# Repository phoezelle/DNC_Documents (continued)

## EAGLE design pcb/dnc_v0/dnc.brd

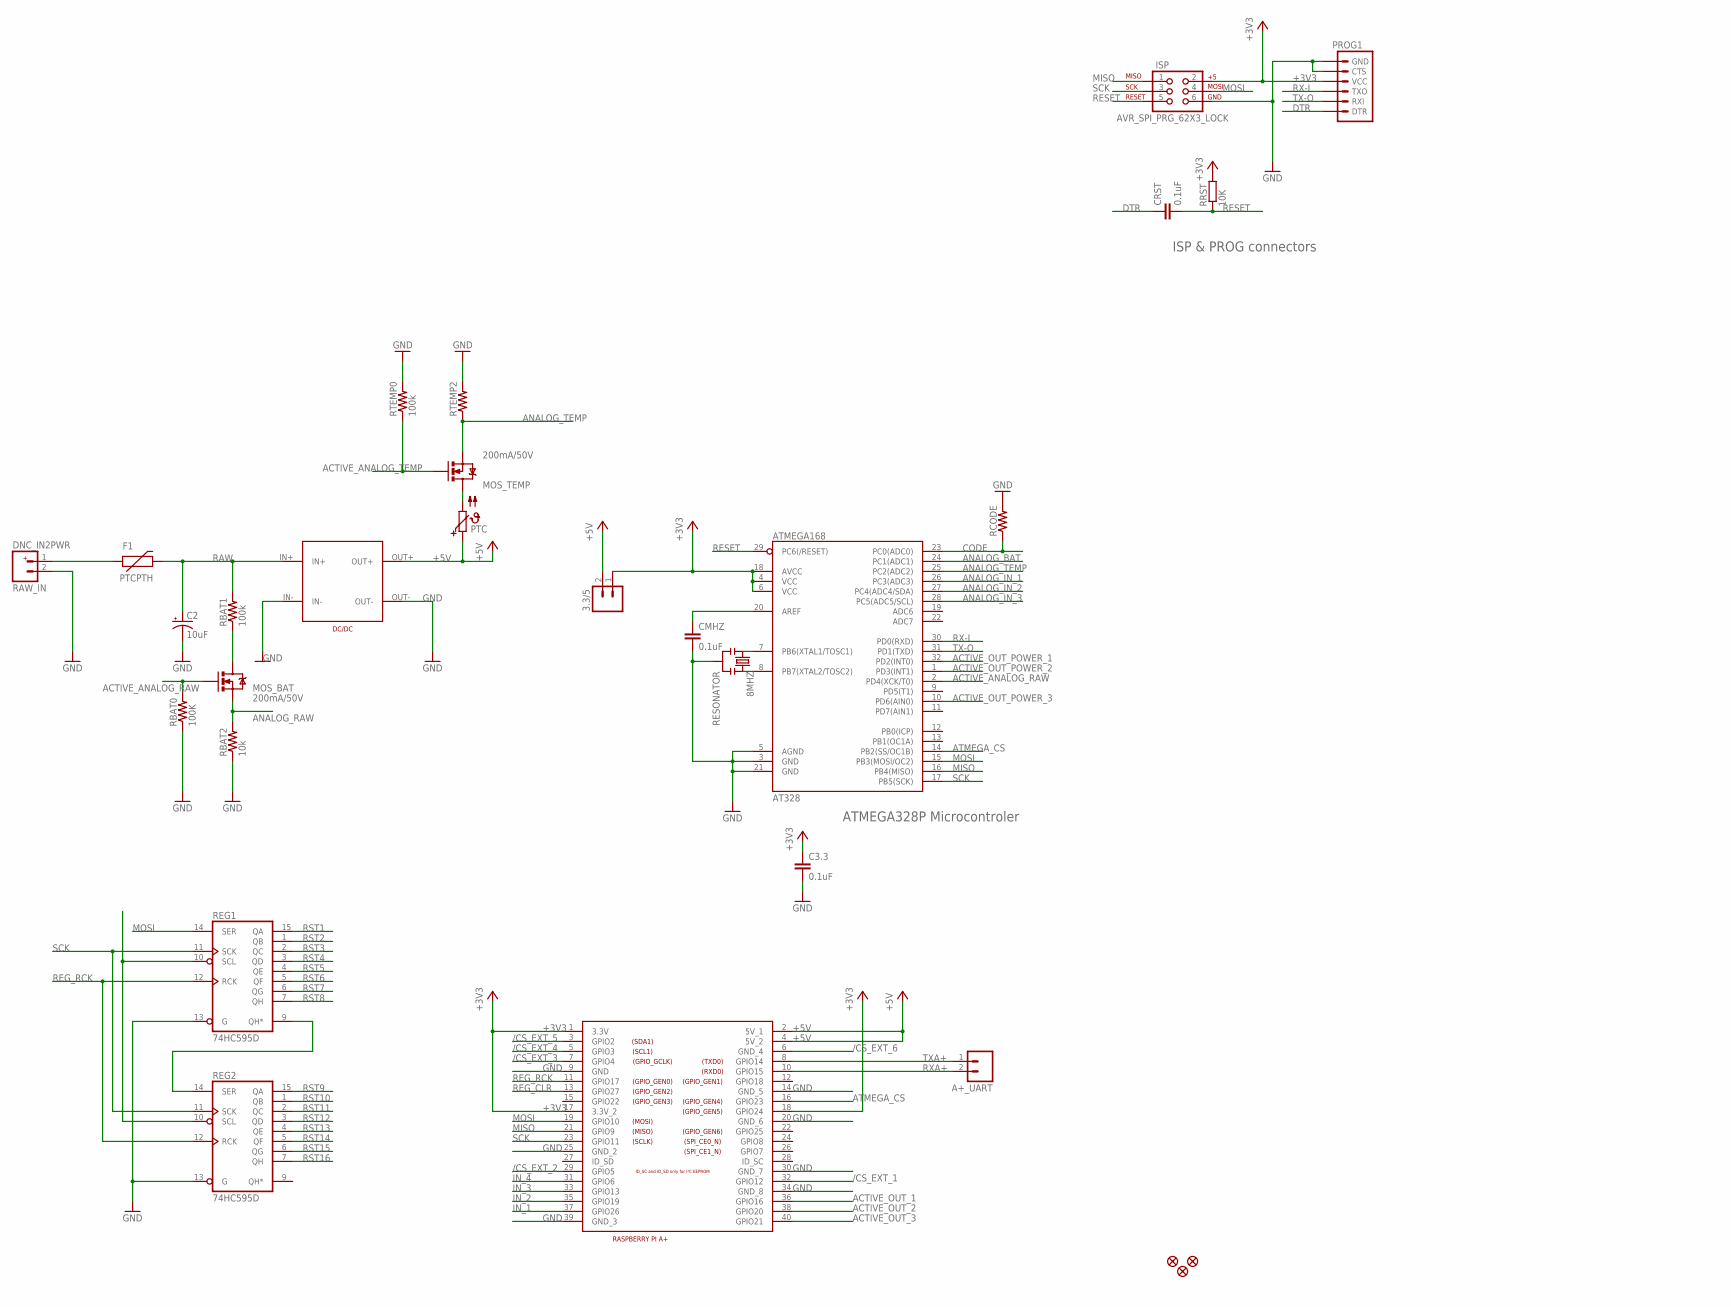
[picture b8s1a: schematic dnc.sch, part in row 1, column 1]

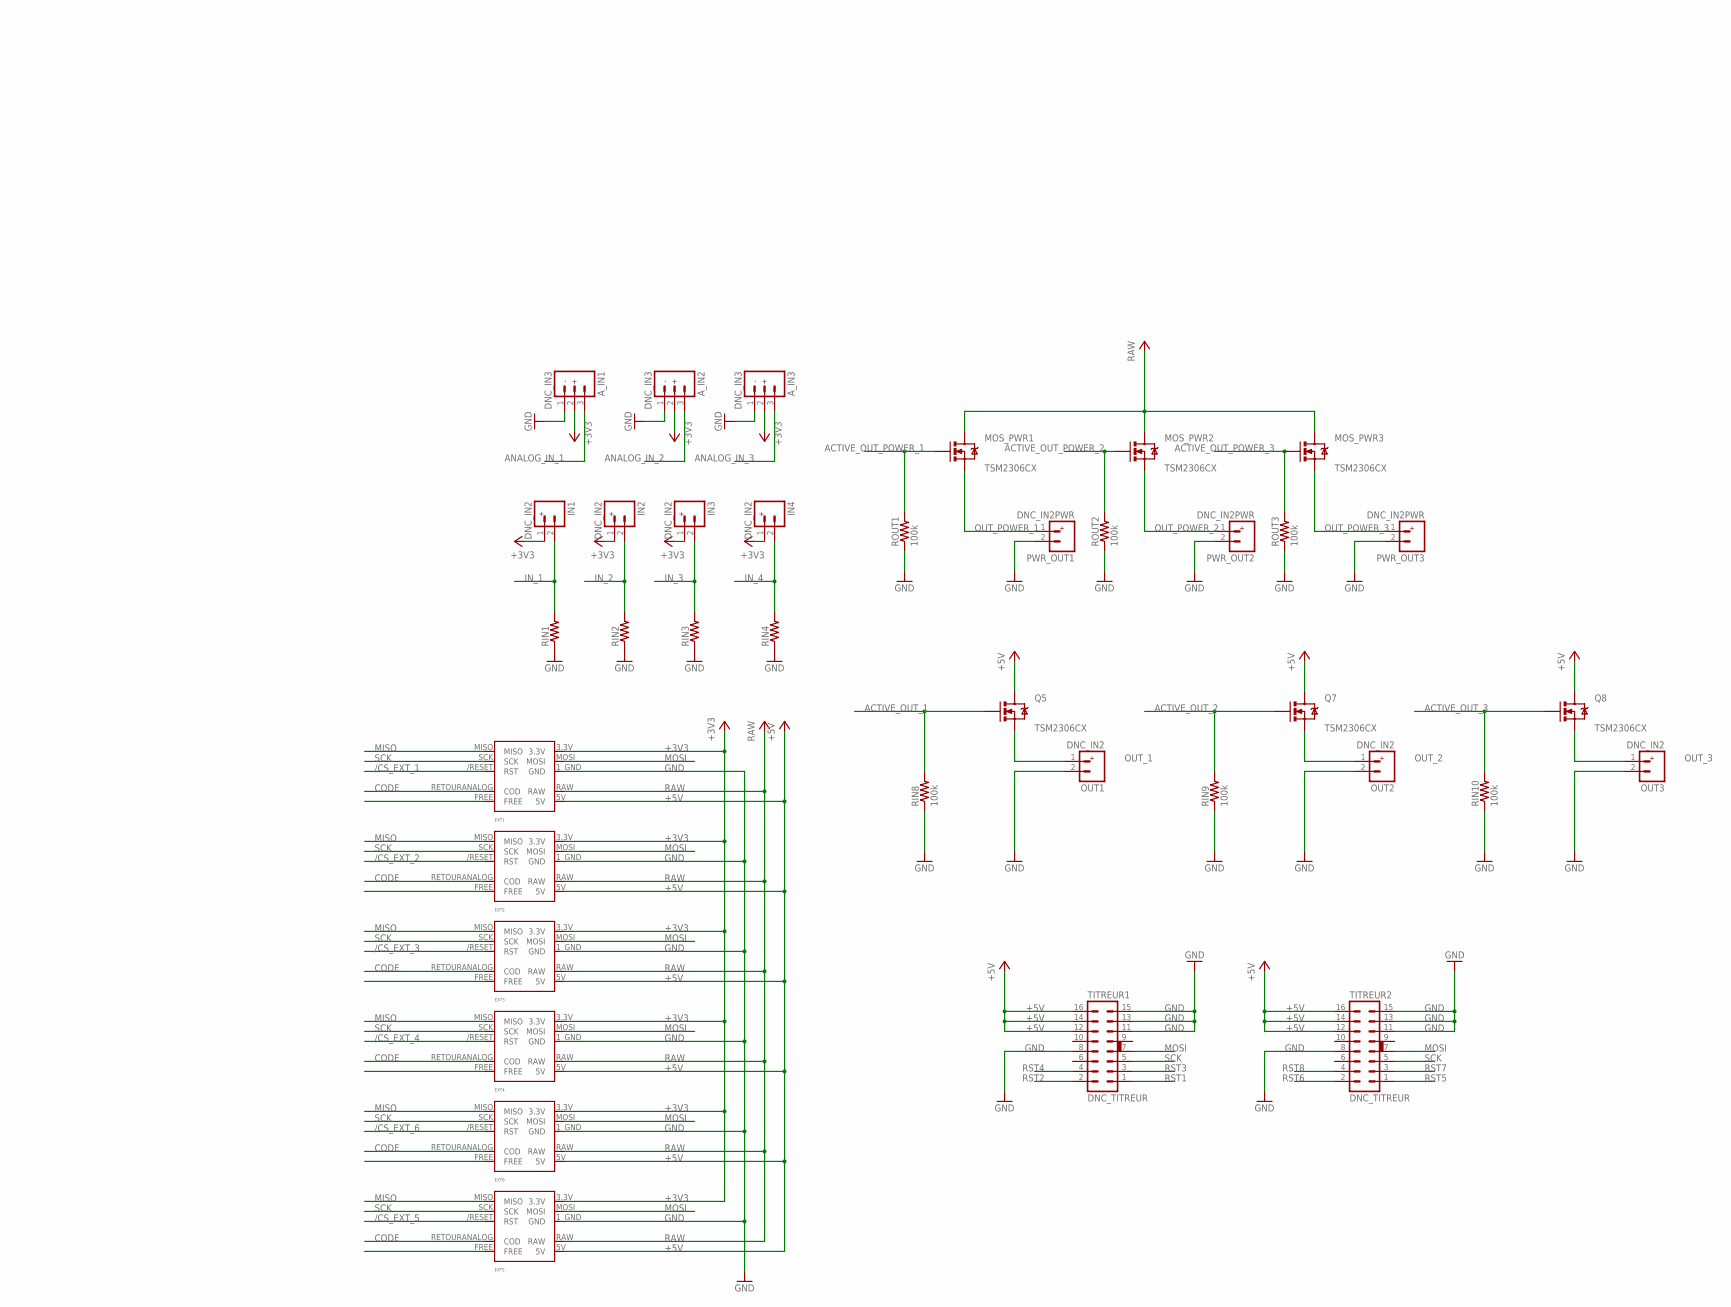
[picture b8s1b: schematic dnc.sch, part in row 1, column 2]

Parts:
3.3/5: M02PTH3; 1X02_LONGPADS
8MHZ: RESONATOR; RESONATOR_7MM
A+_UART: M02LOCK_LONGPADS; 1X02_LOCK_LONGPADS
AT328: ATMEGA168; TQFP32-08
A_IN1, A_IN2, A_IN3: DNC_IN3
C2: 10uF; EIA3216
C3.3: 0.1uF; C0805
CMHZ: 0.1uF; C0805
CRST: 0.1uF; C0805
EXT1, EXT2, EXT3, EXT4, EXT5, EXT6: EXT-DNC; EXTPINDNC
F1: PTCPTH; PTC
IN1, IN2, IN3, IN4: DNC_IN2
ISP: AVR_SPI_PRG_62X3_LOCK; 2X3_LOCK
JP13, JP14, JP19: FIDUCIAL1X2.5; FIDUCIAL-1X2.5
MOS_BAT: 200mA/50V; SOT23-3
MOS_PWR1, MOS_PWR2, MOS_PWR3: TSM2306CX; SOT323
MOS_TEMP: 200mA/50V; SOT23-3
OUT1, OUT2, OUT3: DNC_IN2
PROG1: ARDUINO_SERIAL_PROGRAMLOCK; 1X06_LOCK
PTC: PTC679; P679
PWR_OUT1, PWR_OUT2, PWR_OUT3: DNC_IN2PWR; DNC_IN2_PWR
Q5, Q7, Q8: TSM2306CX; SOT323
RAW_IN: DNC_IN2PWR; DNC_IN2_PWR
RBAT0: 100K; 0603-RES
RBAT1: 100k; 0603-RES
RBAT2: 10k; 0603-RES
RCODE: RESISTOR0603-RES; 0603-RES
REG1, REG2: 74HC595D; SO16
RIN1, RIN2, RIN3, RIN4: RESISTOR0603-RES; 0603-RES
RIN8, RIN9, RIN10: 100k; 0603-RES
ROUT1, ROUT2, ROUT3: 100k; 0603-RES
RRST: 10K; R0603
RTEMP0: 100k; 0603-RES
RTEMP2: RESISTOR0603-RES; 0603-RES
TITREUR1, TITREUR2: DNC_TITREUR
U$4: RASPIA+
U$5: DC/DC_SEED

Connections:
+3V3: 3.3/5.1, AT328.4 (VCC), AT328.6 (VCC), AT328.18 (AVCC), A_IN1.2, A_IN2.2, A_IN3.2, C3.3.1, EXT1.3.3V, EXT2.3.3V, EXT3.3.3V, EXT4.3.3V, EXT5.3.3V, EXT6.3.3V, IN1.1, IN2.1, IN3.1, IN4.1, ISP.2, PROG1.4 (VCC), RRST.2, U$4.1 (3.3V), U$4.17 (3.3V_2), U$4.18 (GPIO24)
+5V: 3.3/5.2, EXT1.5V, EXT2.5V, EXT3.5V, EXT4.5V, EXT5.5V, EXT6.5V, PTC.1, Q5.3 (D), Q7.3 (D), Q8.3 (D), TITREUR1.12, TITREUR1.14, TITREUR1.16, TITREUR2.12, TITREUR2.14, TITREUR2.16, U$4.2 (5V_1), U$4.4 (5V_2), U$5.OUT+
/CS_EXT_1: EXT1./RESET (RST), U$4.32 (GPIO12)
/CS_EXT_2: EXT2./RESET (RST), U$4.29 (GPIO5)
/CS_EXT_3: EXT3./RESET (RST), U$4.7 (GPIO4)
/CS_EXT_4: EXT4./RESET (RST), U$4.5 (GPIO3)
/CS_EXT_5: EXT5./RESET (RST), U$4.3 (GPIO2)
/CS_EXT_6: EXT6./RESET (RST), U$4.6 (GND_4)
ACTIVE_ANALOG_RAW: AT328.2 (PD4(XCK/T0)), MOS_BAT.1 (G), RBAT0.2
ACTIVE_ANALOG_TEMP: MOS_TEMP.1 (G), RTEMP0.1
ACTIVE_OUT_1: Q5.1 (G), RIN8.2, U$4.36 (GPIO16)
ACTIVE_OUT_2: Q7.1 (G), RIN9.2, U$4.38 (GPIO20)
ACTIVE_OUT_3: Q8.1 (G), RIN10.2, U$4.40 (GPIO21)
ACTIVE_OUT_POWER_1: AT328.32 (PD2(INT0)), MOS_PWR1.1 (G), ROUT1.2
ACTIVE_OUT_POWER_2: AT328.1 (PD3(INT1)), MOS_PWR2.1 (G), ROUT2.2
ACTIVE_OUT_POWER_3: AT328.10 (PD6(AIN0)), MOS_PWR3.1 (G), ROUT3.2
ANALOG_BAT: AT328.24 (PC1(ADC1))
ANALOG_IN_1: AT328.26 (PC3(ADC3)), A_IN1.3
ANALOG_IN_2: AT328.27 (PC4(ADC4/SDA)), A_IN2.3
ANALOG_IN_3: AT328.28 (PC5(ADC5/SCL)), A_IN3.3
ANALOG_RAW: MOS_BAT.2 (S), RBAT2.2
ANALOG_TEMP: AT328.25 (PC2(ADC2)), MOS_TEMP.2 (S), RTEMP2.1
AREF: AT328.20 (AREF), CMHZ.1
ATMEGA_CS: AT328.14 (PB2(SS/OC1B)), U$4.16 (GPIO23)
CODE: AT328.23 (PC0(ADC0)), EXT1.RETOURANALOG (COD), EXT2.RETOURANALOG (COD), EXT3.RETOURANALOG (COD), EXT4.RETOURANALOG (COD), EXT5.RETOURANALOG (COD), EXT6.RETOURANALOG (COD), RCODE.1
DTR: CRST.1, PROG1.1 (DTR)
GND: 8MHZ.2, AT328.3 (GND), AT328.5 (AGND), AT328.21 (GND), A_IN1.1, A_IN2.1, A_IN3.1, C2.C (-), C3.3.2, CMHZ.2, EXT1.1_GND (GND), EXT2.1_GND (GND), EXT3.1_GND (GND), EXT4.1_GND (GND), EXT5.1_GND (GND), EXT6.1_GND (GND), ISP.6, OUT1.2, OUT2.2, OUT3.2, PROG1.5 (CTS), PROG1.6 (GND), PWR_OUT1.2, PWR_OUT2.2, PWR_OUT3.2, RAW_IN.2, RBAT0.1, RBAT2.1, RCODE.2, REG1.8 (GND), REG1.13 (G), REG2.8 (GND), REG2.13 (G), RIN1.1, RIN2.1, RIN3.1, RIN4.1, RIN8.1, RIN9.1, RIN10.1, ROUT1.1, ROUT2.1, ROUT3.1, RTEMP0.2, RTEMP2.2, TITREUR1.8, TITREUR1.11, TITREUR1.13, TITREUR1.15, TITREUR2.8, TITREUR2.11, TITREUR2.13, TITREUR2.15, U$4.9 (GND), U$4.14 (GND_5), U$4.20 (GND_6), U$4.25 (GND_2), U$4.30 (GND_7), U$4.34 (GND_8), U$4.39 (GND_3), U$5.IN-, U$5.OUT-
IN_1: IN1.2, RIN1.2, U$4.37 (GPIO26)
IN_2: IN2.2, RIN2.2, U$4.35 (GPIO19)
IN_3: IN3.2, RIN3.2, U$4.33 (GPIO13)
IN_4: IN4.2, RIN4.2, U$4.31 (GPIO6)
MISO: AT328.16 (PB4(MISO)), EXT1.MISO, EXT2.MISO, EXT3.MISO, EXT4.MISO, EXT5.MISO, EXT6.MISO, ISP.1, U$4.21 (GPIO9)
MOSI: AT328.15 (PB3(MOSI/OC2)), EXT1.MOSI, EXT2.MOSI, EXT3.MOSI, EXT4.MOSI, EXT5.MOSI, EXT6.MOSI, ISP.4, REG1.14 (SER), TITREUR1.7, TITREUR2.7, U$4.19 (GPIO10)
unnamed: MOS_BAT.3 (D), RBAT1.1
unnamed: REG1.9 (QH*), REG2.14 (SER)
unnamed: MOS_TEMP.3 (D), PTC.2
unnamed: F1.P$1 (1), RAW_IN.1
unnamed: 8MHZ.1, AT328.7 (PB6(XTAL1/TOSC1))
unnamed: 8MHZ.3, AT328.8 (PB7(XTAL2/TOSC2))
OUT_1: OUT1.1, Q5.2 (S)
OUT_2: OUT2.1, Q7.2 (S)
OUT_3: OUT3.1, Q8.2 (S)
OUT_POWER_1: MOS_PWR1.2 (S), PWR_OUT1.1
OUT_POWER_2: MOS_PWR2.2 (S), PWR_OUT2.1
OUT_POWER_3: MOS_PWR3.2 (S), PWR_OUT3.1
RAW: C2.A (+), EXT1.RAW, EXT2.RAW, EXT3.RAW, EXT4.RAW, EXT5.RAW, EXT6.RAW, F1.P$2 (2), MOS_PWR1.3 (D), MOS_PWR2.3 (D), MOS_PWR3.3 (D), RBAT1.2, U$5.IN+
REG_CLR: REG1.10 (SCL), REG2.10 (SCL), U$4.13 (GPIO27)
REG_RCK: REG1.12 (RCK), REG2.12 (RCK), U$4.11 (GPIO17)
RESET: AT328.29 (PC6(/RESET)), CRST.2, ISP.5, RRST.1
RST1: REG1.15 (QA), TITREUR1.1
RST2: REG1.1 (QB), TITREUR1.2
RST3: REG1.2 (QC), TITREUR1.3
RST4: REG1.3 (QD), TITREUR1.4
RST5: REG1.4 (QE), TITREUR2.1
RST6: REG1.5 (QF), TITREUR2.2
RST7: REG1.6 (QG), TITREUR2.3
RST8: REG1.7 (QH), TITREUR2.4
RST9: REG2.15 (QA)
RST10: REG2.1 (QB)
RST11: REG2.2 (QC)
RST12: REG2.3 (QD)
RST13: REG2.4 (QE)
RST14: REG2.5 (QF)
RST15: REG2.6 (QG)
RST16: REG2.7 (QH)
RX-I: AT328.30 (PD0(RXD)), PROG1.3 (TXO)
RXA+: A+_UART.2, U$4.10 (GPIO15)
SCK: AT328.17 (PB5(SCK)), EXT1.SCK, EXT2.SCK, EXT3.SCK, EXT4.SCK, EXT5.SCK, EXT6.SCK, ISP.3, REG1.11 (SCK), REG2.11 (SCK), TITREUR1.5, TITREUR2.5, U$4.23 (GPIO11)
TX-O: AT328.31 (PD1(TXD)), PROG1.2 (RXI)
TXA+: A+_UART.1, U$4.8 (GPIO14)
VCC: REG1.16 (VCC), REG2.16 (VCC)

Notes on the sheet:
ATMEGA328P Microcontroler
ISP & PROG connectors

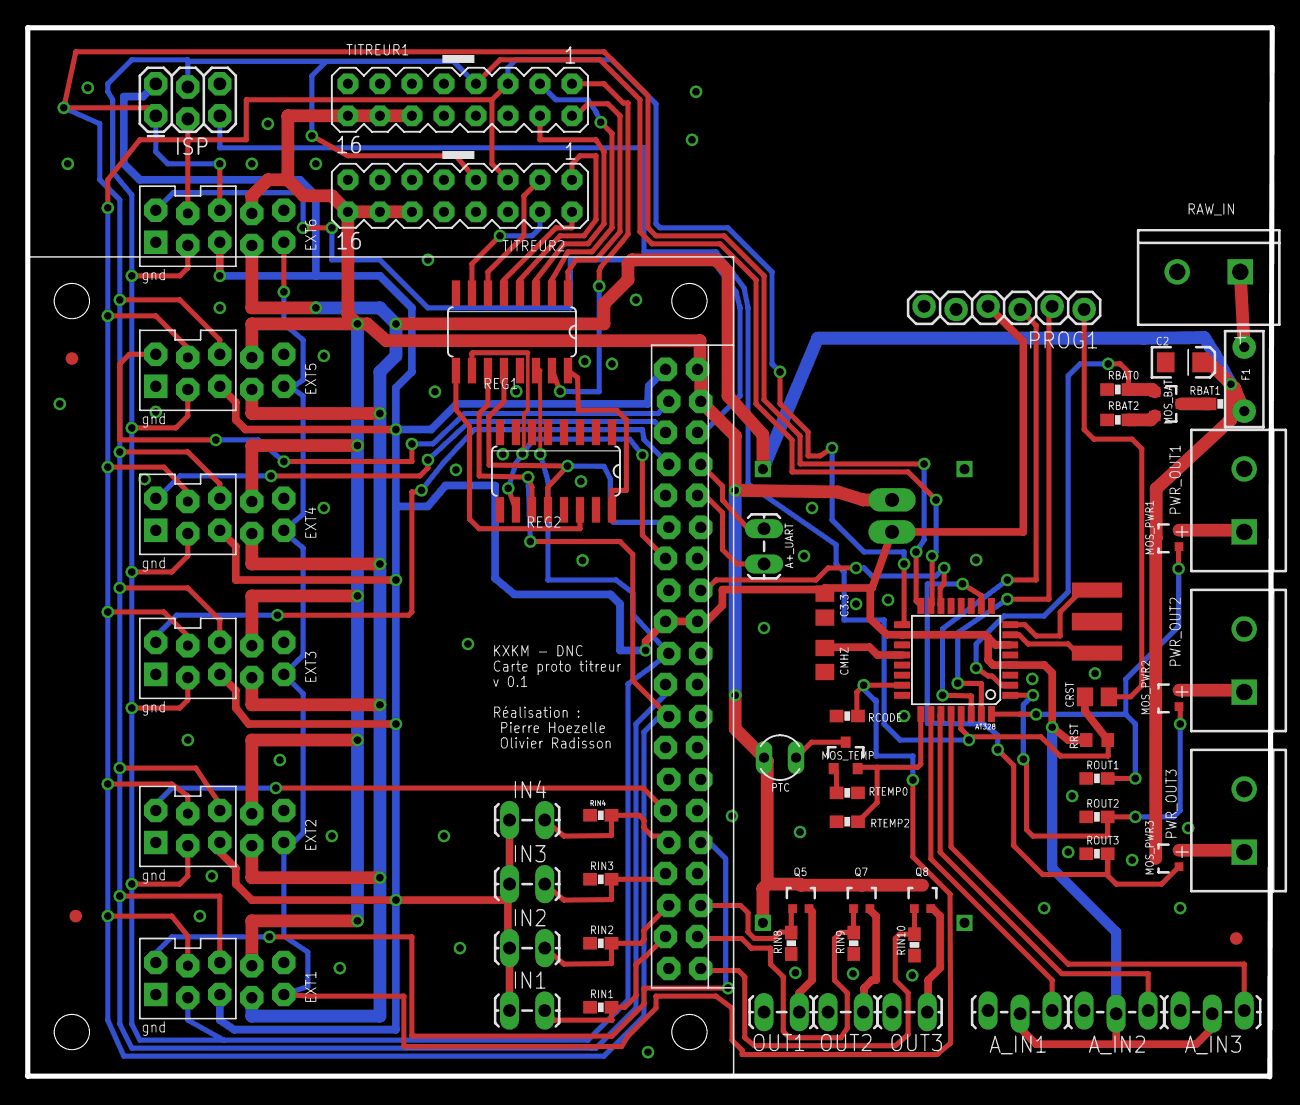
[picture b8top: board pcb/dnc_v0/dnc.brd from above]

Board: 2 copper layers, 98.7 x 83.2 mm, 66 parts (0 on the bottom side), 62 nets.

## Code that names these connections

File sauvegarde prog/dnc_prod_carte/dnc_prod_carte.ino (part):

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#define LED10W2VALUE 4
#define INTERRUPT 5
//VALUE FOR PININ
#define PUSH1 6
#define PUSH2 7
#define PUSH3 8
//VALUE FOR PININ ANALOG
#define FLOAT 9
#define UBATT 10
#define CODE 11
//RVB
#define LEDRVBSTROBSPEED 12
#define LEDRVBMODE 13
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

void readTensionBatt() {
  int batt = analogRead(inpinanalog[UBATT - DECALALOGPIN]);
  if (Value[VOLTAGEMODE] == 0) {
    if (batt < 320) newValue[VOLTAGEMODE] = 12;
    else newValue[VOLTAGEMODE] = 24;
  }
  long voltage;
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
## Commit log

2014-09-22 Ajout d'une legende
2014-09-23 add doc
2014-09-24 Avance et ajout de référence pour chaque pin
2014-09-24 Ajout d'une page pour le calcul des codes d'extension
2014-09-26 Ajout d'une première proposition pour l'organisation de la carte (software)
2014-10-07 proposition annoté par pierre
2014-10-09 ajout d'un todo
2014-11-17 ajout du fichier eagle + début pinmap 328
2014-11-18 draw yunshield eagle-objet in a eaglelib pcb add sunshield eagle file in docref
2014-11-18 add arduino pro eagle in doc ref
2014-11-18 Add HC595 datasheey
2014-11-19 Avancée sur eagle
2014-11-19 nouvelle donne rasberry dans le fichier ods + lib eagle small gpio
2014-11-19 add ext objet in eagle lib
2014-11-19 Ajout d'un element RASPIA+
2014-11-19 Début de la modification pour RASPIA+
2014-11-19 Update RASPIA+ device
2014-11-19 Add DC/DC SEED convertor
2014-11-19 Progression sur le sch : 6x10pin + DC/DC + ANALOG_BAT
2014-11-19 Add Temp sensor and two 74HC595 for titreur select
2014-11-19 Add 3 power output (ugly)
2014-11-19 Add 4 digital input and 3 analog input
2014-11-19 Correct MOSFET
2014-11-19 Ajout d'une ref MOFSET
2014-11-19 Reogranise Sch + Add headers
2014-11-20 changement de plie de package + liste des composants en stock
2014-11-20 a jour
2014-11-20 Add BCM2835-ARM RasPi Proc datasheet
2014-11-20 Reorganize ATmega to work with 5V with tension divider
2014-11-20 Reorganize ATmega to work with 5V with Zener diode
2014-11-20 Reorganize ATmega to work with 3.3V
2014-11-20 Add RaspB+ schem and mechanical
2014-11-20 Add Rasp AB schem
2014-11-20 Reogranise with 3.3, 5 and RAW
2014-11-20 Some little corrections
2014-11-20 Add PTC ref
2014-11-20 Clean dnc_v0 directory
2014-11-24 Correct some big mistackes on schematics, and lib
2014-11-24 First try of routing, no analog atmega ?
2014-11-24 Add a small link
2014-11-24 End (100%) first try, but no analog !
2014-11-24 New brd far better, but not finished
2014-11-24 Little improvement
2014-11-25 Manual brd just before GND
2014-11-25 Add NAND ref
2014-11-25 Place labels
2014-11-27 Route finished, first version
2014-11-27 Ajout de doc ref et d'essai ISIS
2014-11-27 Update lib and clean up the brd
2014-11-27 Add a titreur only sch and brd
2014-12-01 Finished brd before first print
2014-12-02 commande pcb passée
2014-12-13 première extension info + listing dispo
2014-12-13 ajout des infos de la rué sur le soft de contrôle -ihm.jpeg note.odt
2014-12-21 add documentation
2014-12-27 mise à jour du budget, début 2ème carte
2014-12-28 avance sur v1
2014-12-31 in progress
2014-12-31 in progress 2
2015-01-02 schematic fini début routage
2015-01-07 routage terminé
2015-01-09 Rédaction des propositions pour la doc
2015-01-14 maj + ajout rs232
2015-01-15 clean board
2015-01-16 rj45 au dessus
2015-01-16 good size
2015-01-22 maj 22 janv
2015-01-22 ajout ampli
2015-01-23 carte extension chargeur LIPO
2015-01-27 add remote + enclosure
2015-02-03 BOM + carte insa
2015-02-10 minor debug (hole + value)
2015-02-11 BOM ext teleco et chargeur
2015-02-17 major change correction : - driver led position - add usb for power - correct max 202 voltage problem - titrer connector position - forget line - power trace consideration
2015-02-17 fix text place and size
2015-02-18 minor change : - logo size - add fuse on led - enclosure
2015-02-26 change minor : - add rj45 for led string - add select pam led or flex
2015-03-20 major changes : - carte pieuvre - carte relais - correctif v1 : usb + pin A7 ! - enclosure
2015-03-23 add prog copy
2015-03-27 add telco sauvegarde prig
2015-09-15 maj sept 2015
